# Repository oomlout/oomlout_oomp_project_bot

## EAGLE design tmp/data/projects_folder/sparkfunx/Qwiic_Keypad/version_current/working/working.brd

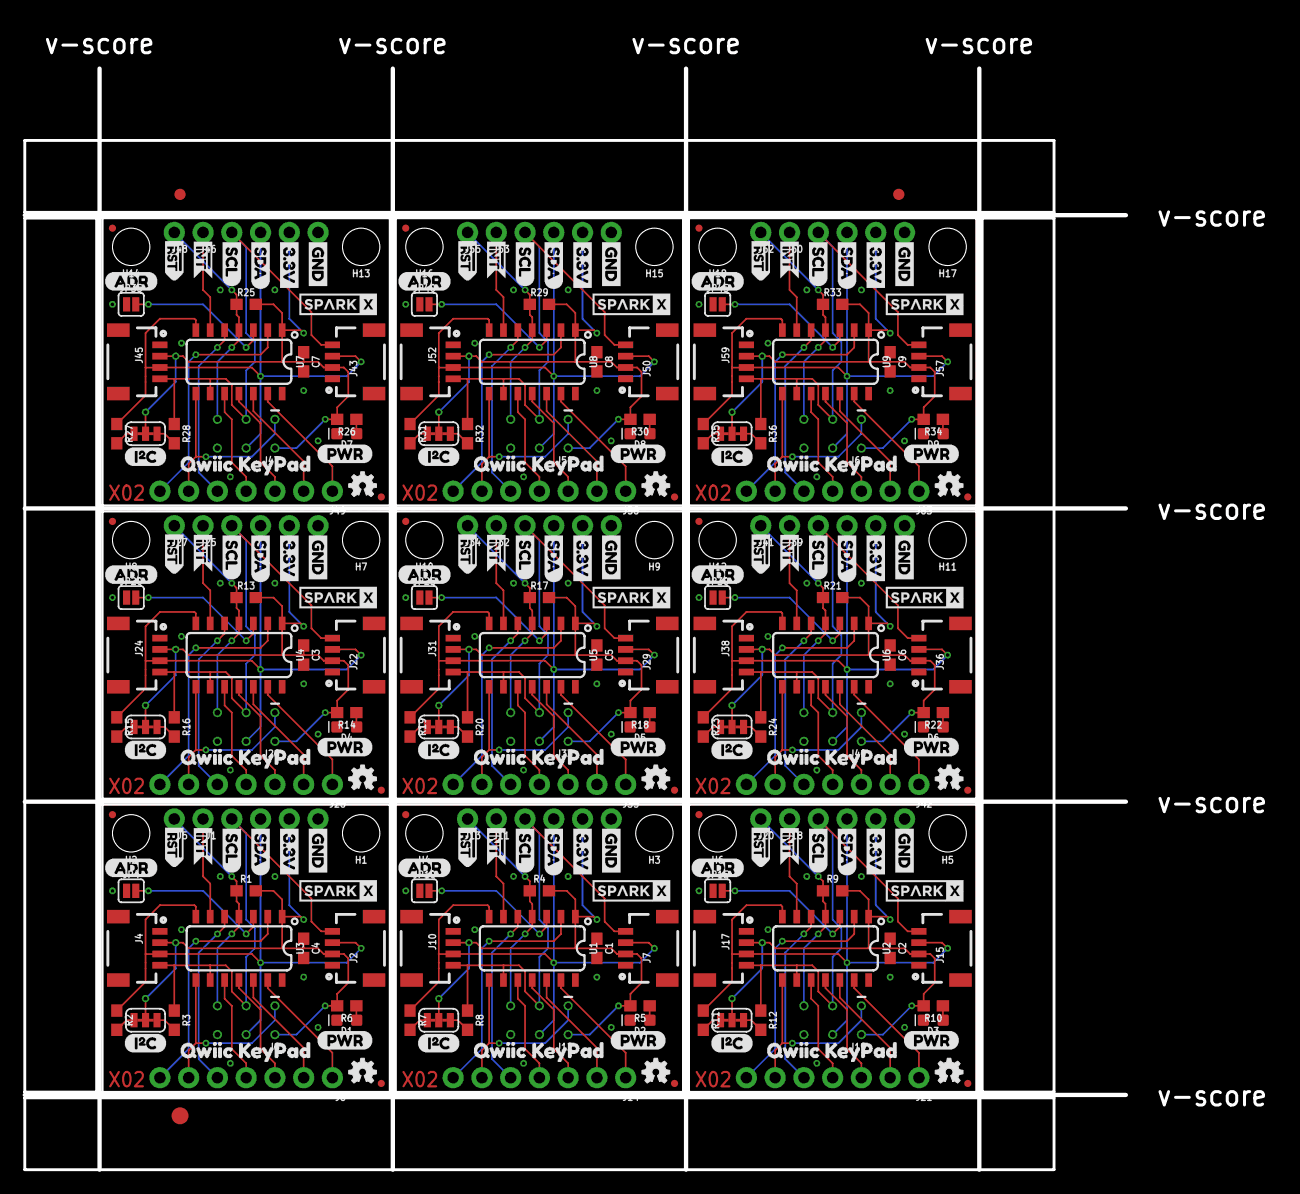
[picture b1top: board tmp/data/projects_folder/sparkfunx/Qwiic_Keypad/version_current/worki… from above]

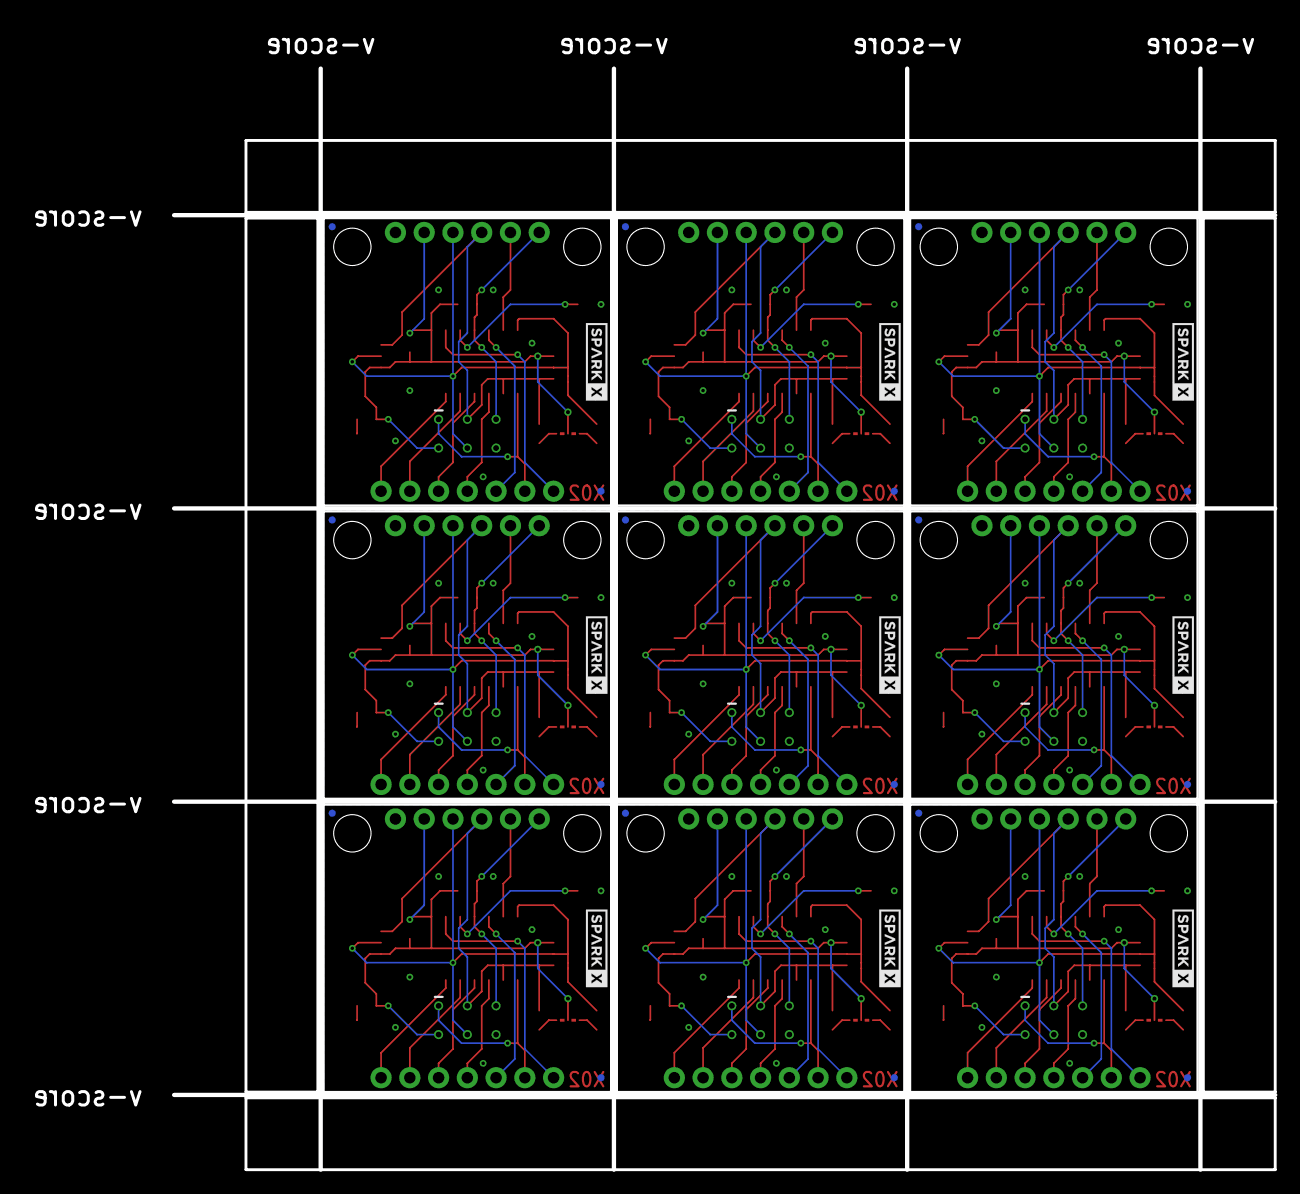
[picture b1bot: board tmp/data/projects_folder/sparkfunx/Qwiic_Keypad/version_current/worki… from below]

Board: 2 copper layers, 97.3 x 97.3 mm, 318 parts (27 on the bottom side), 153 nets.

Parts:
C1, C2, C3, C4, C5, C6, C7, C8, C9: 0.1uF; 0603
D1, D2, D3, D4, D5, D6, D7, D8, D9: RED; LED-0603
E$1, E$2: FIDUCIAL-1X2
E$3: FIDUCIAL-1.5X3
H1, H2, H3, H4, H5, H6, H7, H8, H9, H10, H11, H12, H13, H14, H15, H16, H17, H18: STAND-OFF
J1, J5, J11, J13, J18, J20, J25, J27, J32, J34, J39, J41, J46, J48, J53, J55, J60, J62: 1X01_NO_SILK
J2, J4, J7, J10, J15, J17, J22, J24, J29, J31, J36, J38, J43, J45, J50, J52, J57, J59: 1X04_1MM_RA
J3, J9, J16, J23, J30, J37, J44, J51, J58: PTH; 1X04_NO_SILK
J6, J12, J19, J26, J33, J40, J47, J54, J61: AVR_SPI_PROG_3X2TESTPOINTS; 2X3_TEST_POINTS
J8, J14, J21, J28, J35, J42, J49, J56, J63: 1X07_NO_SILK
JP1, JP2, JP3, JP5, JP6, JP7, JP8, JP9, JP11, JP12, JP13, JP14, JP16, JP17, JP18, JP19, JP21, JP22, JP23, JP24, JP26, JP27, JP28, JP29, JP31, JP32, JP33, JP34, JP36, JP37, JP38, JP39, JP41, JP42, JP43, JP44: FIDUCIALUFIDUCIAL; MICRO-FIDUCIAL
JP4, JP10, JP15, JP20, JP25, JP30, JP35, JP40, JP45: SMT-JUMPER_2_NO_SILK
LOGO1, LOGO2, LOGO3, LOGO4, LOGO5, LOGO6, LOGO7, LOGO8, LOGO9: OSHW-LOGOMINI; OSHW-LOGO-MINI
R1, R4, R9, R13, R17, R21, R25, R29, R33: 4.7k; 0603
R2, R3, R7, R8, R11, R12, R15, R16, R19, R20, R23, R24, R27, R28, R31, R32, R35, R36: 2.2k; 0603
R5, R6, R10, R14, R18, R22, R26, R30, R34: 1k; 0603
SJ1, SJ2, SJ3, SJ4, SJ5, SJ6, SJ7, SJ8, SJ9: SMT-JUMPER_3_2-NC_TRACE_SILK
U1, U2, U3, U4, U5, U6, U7, U8, U9: ATTINY84; SO14
U$1, U$2, U$7, U$13, U$25, U$26, U$37, U$38, U$49, U$50, U$61, U$62, U$73, U$74, U$85, U$86, U$97, U$98: SPARKX-LOGO3; SPARKX-SMALL
U$3, U$14, U$27, U$39, U$51, U$63, U$75, U$87, U$99: 3.3V
U$4, U$16, U$28, U$40, U$52, U$64, U$76, U$88, U$100: GND
U$5, U$17, U$29, U$41, U$53, U$65, U$77, U$89, U$101: SDA
U$6, U$18, U$30, U$42, U$54, U$66, U$78, U$90, U$102: SCL
U$8, U$19, U$31, U$43, U$55, U$67, U$79, U$91, U$103: (PWR)
U$9, U$20, U$32, U$44, U$56, U$68, U$80, U$92, U$104: (I_SUPER2_C)
U$10, U$21, U$33, U$45, U$57, U$69, U$81, U$93, U$105: (ADR)
U$11, U$22, U$34, U$46, U$58, U$70, U$82, U$94, U$106: #RST>
U$12, U$24, U$36, U$48, U$60, U$72, U$84, U$96, U$108: #INT1
U$15, U$23, U$35, U$47, U$59, U$71, U$83, U$95, U$107: QWIIC_KEYPAD0

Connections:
1: J8.1, U3.13
2: J8.2, U3.12
3: J8.3, U3.11
3.3V: C4.1, J2.2, J3.2, J4.2, J6.2, R1.2, R6.2, SJ5.2, U3.1
3.3V1: C1.1, J7.2, J9.2, J10.2, J12.2, R4.2, R5.2, SJ1.2, U1.1
3.3V2: C2.1, J15.2, J16.2, J17.2, J19.2, R9.2, R10.2, SJ2.2, U2.1
3.3V3: C3.1, J22.2, J23.2, J24.2, J26.2, R13.2, R14.2, SJ3.2, U4.1
3.3V4: C5.1, J29.2, J30.2, J31.2, J33.2, R17.2, R18.2, SJ4.2, U5.1
3.3V5: C6.1, J36.2, J37.2, J38.2, J40.2, R21.2, R22.2, SJ6.2, U6.1
3.3V6: C7.1, J43.2, J44.2, J45.2, J47.2, R25.2, R26.2, SJ7.2, U7.1
3.3V7: C8.1, J50.2, J51.2, J52.2, J54.2, R29.2, R30.2, SJ8.2, U8.1
3.3V8: C9.1, J57.2, J58.2, J59.2, J61.2, R33.2, R34.2, SJ9.2, U9.1
4: J8.4, U3.10
5: J8.5, U3.5
6: J14.4, U1.10
7: J8.7, U3.2
8: J14.3, U1.11
9: J14.2, U1.12
10: J14.1, U1.13
11: J14.7, U1.2
12: J14.5, U1.5
13: J21.4, U2.10
14: J21.3, U2.11
15: J21.2, U2.12
16: J21.1, U2.13
17: J21.7, U2.2
18: J21.5, U2.5
19: J28.4, U4.10
20: J28.3, U4.11
21: J28.2, U4.12
22: J28.1, U4.13
23: J28.7, U4.2
24: J28.5, U4.5
25: J35.4, U5.10
26: J35.3, U5.11
27: J35.2, U5.12
28: J35.1, U5.13
29: J35.7, U5.2
30: J35.5, U5.5
31: J42.4, U6.10
32: J42.3, U6.11
33: J42.2, U6.12
34: J42.1, U6.13
35: J42.7, U6.2
36: J42.5, U6.5
37: J49.4, U7.10
38: J49.3, U7.11
39: J49.2, U7.12
40: J49.1, U7.13
41: J49.7, U7.2
42: J49.5, U7.5
43: J56.4, U8.10
44: J56.3, U8.11
45: J56.2, U8.12
46: J56.1, U8.13
47: J56.7, U8.2
48: J56.5, U8.5
49: J63.4, U9.10
50: J63.3, U9.11
51: J63.2, U9.12
52: J63.1, U9.13
53: J63.7, U9.2
54: J63.5, U9.5
!INT: J1.1, U3.6
!INT1: J11.1, U1.6
!INT2: J18.1, U2.6
!INT3: J25.1, U4.6
!INT4: J32.1, U5.6
!INT5: J39.1, U6.6
!INT6: J46.1, U7.6
!INT7: J53.1, U8.6
!INT8: J60.1, U9.6
!RST: J5.1, J6.5, R1.1, U3.4
!RST1: J12.5, J13.1, R4.1, U1.4
!RST2: J19.5, J20.1, R9.1, U2.4
!RST3: J26.5, J27.1, R13.1, U4.4
!RST4: J33.5, J34.1, R17.1, U5.4
!RST5: J40.5, J41.1, R21.1, U6.4
!RST6: J47.5, J48.1, R25.1, U7.4
!RST7: J54.5, J55.1, R29.1, U8.4
!RST8: J61.5, J62.1, R33.1, U9.4
ADD1: JP4.2, U3.3
ADD2: JP10.2, U1.3
ADD3: JP15.2, U2.3
ADD4: JP20.2, U4.3
ADD5: JP25.2, U5.3
ADD6: JP30.2, U6.3
ADD7: JP35.2, U7.3
ADD8: JP40.2, U8.3
ADD9: JP45.2, U9.3
GND: C4.2, D1.C, J2.1, J3.1, J4.1, J6.6, JP4.1, U3.14
GND1: C1.2, D2.C, J7.1, J9.1, J10.1, J12.6, JP10.1, U1.14
GND2: C2.2, D3.C, J15.1, J16.1, J17.1, J19.6, JP15.1, U2.14
GND3: C3.2, D4.C, J22.1, J23.1, J24.1, J26.6, JP20.1, U4.14
GND4: C5.2, D5.C, J29.1, J30.1, J31.1, J33.6, JP25.1, U5.14
GND5: C6.2, D6.C, J36.1, J37.1, J38.1, J40.6, JP30.1, U6.14
GND6: C7.2, D7.C, J43.1, J44.1, J45.1, J47.6, JP35.1, U7.14
GND7: C8.2, D8.C, J50.1, J51.1, J52.1, J54.6, JP40.1, U8.14
GND8: C9.2, D9.C, J57.1, J58.1, J59.1, J61.6, JP45.1, U9.14
MISO/1: J12.1, J14.6, U1.8
MISO/2: J19.1, J21.6, U2.8
MISO/3: J26.1, J28.6, U4.8
MISO/4: J33.1, J35.6, U5.8
MISO/5: J40.1, J42.6, U6.8
MISO/6: J6.1, J8.6, U3.8
MISO/7: J47.1, J49.6, U7.8
MISO/8: J54.1, J56.6, U8.8
MISO/9: J61.1, J63.6, U9.8
unnamed: D1.A, R6.1
unnamed: R2.2, SJ5.3
unnamed: R3.2, SJ5.1
unnamed: D2.A, R5.1
unnamed: R7.2, SJ1.3
unnamed: R8.2, SJ1.1
unnamed: D3.A, R10.1
unnamed: R11.2, SJ2.3
unnamed: R12.2, SJ2.1
unnamed: D4.A, R14.1
unnamed: R15.2, SJ3.3
unnamed: R16.2, SJ3.1
unnamed: D5.A, R18.1
unnamed: R19.2, SJ4.3
unnamed: R20.2, SJ4.1
unnamed: D6.A, R22.1
unnamed: R23.2, SJ6.3
unnamed: R24.2, SJ6.1
unnamed: D7.A, R26.1
unnamed: R27.2, SJ7.3
unnamed: R28.2, SJ7.1
unnamed: D8.A, R30.1
unnamed: R31.2, SJ8.3
unnamed: R32.2, SJ8.1
unnamed: D9.A, R34.1
unnamed: R35.2, SJ9.3
unnamed: R36.2, SJ9.1
SCL: J2.4, J3.4, J4.4, J6.3, R3.1, U3.9
SCL1: J7.4, J9.4, J10.4, J12.3, R8.1, U1.9
SCL2: J15.4, J16.4, J17.4, J19.3, R12.1, U2.9
SCL3: J22.4, J23.4, J24.4, J26.3, R16.1, U4.9
SCL4: J29.4, J30.4, J31.4, J33.3, R20.1, U5.9
SCL5: J36.4, J37.4, J38.4, J40.3, R24.1, U6.9
SCL6: J43.4, J44.4, J45.4, J47.3, R28.1, U7.9
SCL7: J50.4, J51.4, J52.4, J54.3, R32.1, U8.9
SCL8: J57.4, J58.4, J59.4, J61.3, R36.1, U9.9
SDA: J2.3, J3.3, J4.3, J6.4, R2.1, U3.7
SDA1: J7.3, J9.3, J10.3, J12.4, R7.1, U1.7
SDA2: J15.3, J16.3, J17.3, J19.4, R11.1, U2.7
SDA3: J22.3, J23.3, J24.3, J26.4, R15.1, U4.7
SDA4: J29.3, J30.3, J31.3, J33.4, R19.1, U5.7
SDA5: J36.3, J37.3, J38.3, J40.4, R23.1, U6.7
SDA6: J43.3, J44.3, J45.3, J47.4, R27.1, U7.7
SDA7: J50.3, J51.3, J52.3, J54.4, R31.1, U8.7
SDA8: J57.3, J58.3, J59.3, J61.4, R35.1, U9.7

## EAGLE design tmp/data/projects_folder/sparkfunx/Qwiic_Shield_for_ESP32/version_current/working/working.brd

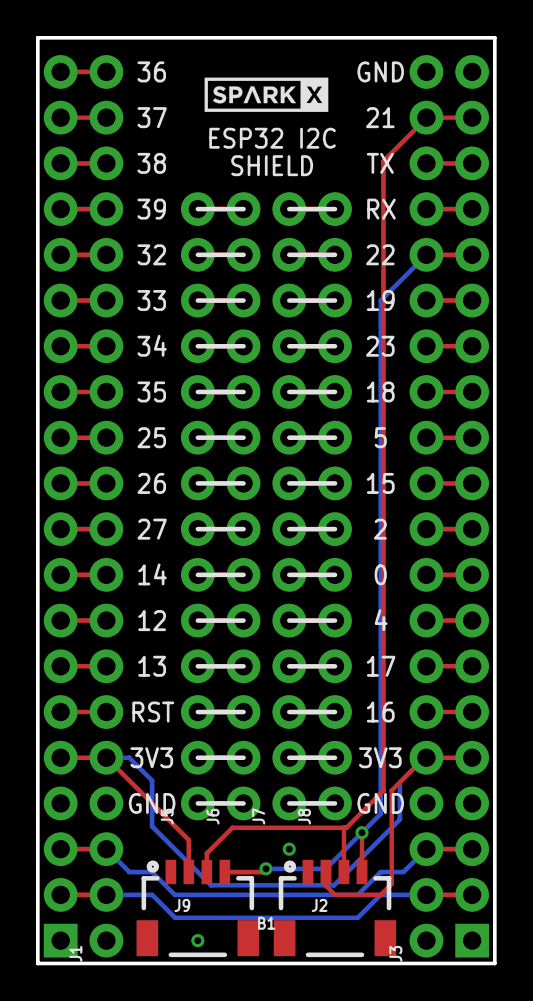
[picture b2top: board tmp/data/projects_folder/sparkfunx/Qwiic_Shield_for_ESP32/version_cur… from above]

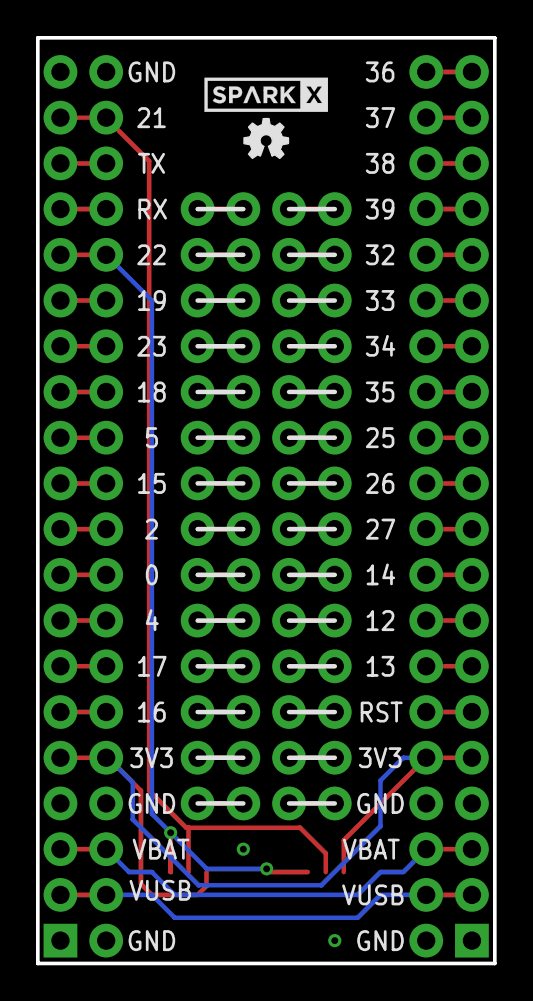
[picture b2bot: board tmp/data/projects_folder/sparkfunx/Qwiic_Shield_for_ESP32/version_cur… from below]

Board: 2 copper layers, 25.4 x 51.4 mm, 13 parts (2 on the bottom side), 61 nets.

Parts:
B1: ESP32_THING
FRAME1: FRAME-LETTERNO_PACKAGE; DUMMY
J1, J3: 1X20_NOSILK
J2, J9: 1X04_1MM_RA
J5, J6, J7, J8: 1X14_NO_SILK
LOGO1: OSHW-LOGOMINI; OSHW-LOGO-MINI
U$1, U$2: SPARKX-LOGO3; SPARKX-SMALL

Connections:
0: B1.32, J3.9
2: B1.31, J3.10
3.3V: B1.5, B1.36, J1.5, J2.2, J3.5, J9.2
4: B1.33, J3.8
5: B1.29, J3.12
12: B1.8, J1.8
13: B1.7, J1.7
14: B1.9, J1.9
15: B1.30, J3.11
16: B1.35, J3.6
17: B1.34, J3.7
25: B1.12, J1.12
26: B1.11, J1.11
27: B1.10, J1.10
32: B1.16, J1.16
33: B1.15, J1.15
34: B1.14, J1.14
35: B1.13, J1.13
36: B1.20, J1.20
37: B1.19, J1.19
38: B1.18, J1.18
39: B1.17, J1.17
GND: B1.1, B1.4, B1.21, B1.37, B1.40, J1.1, J1.4, J2.1, J3.1, J3.4, J3.20, J9.1
MISO: B1.26, J3.15
MOSI: B1.27, J3.14
unnamed: J7.1, J8.1
unnamed: J7.2, J8.2
unnamed: J7.3, J8.3
unnamed: J7.4, J8.4
unnamed: J7.5, J8.5
unnamed: J7.6, J8.6
unnamed: J7.7, J8.7
unnamed: J7.8, J8.8
unnamed: J7.9, J8.9
unnamed: J7.10, J8.10
unnamed: J7.11, J8.11
unnamed: J7.12, J8.12
unnamed: J7.13, J8.13
unnamed: J7.14, J8.14
unnamed: J5.1, J6.1
unnamed: J5.2, J6.2
unnamed: J5.3, J6.3
unnamed: J5.4, J6.4
unnamed: J5.5, J6.5
unnamed: J5.6, J6.6
unnamed: J5.7, J6.7
unnamed: J5.8, J6.8
unnamed: J5.9, J6.9
unnamed: J5.10, J6.10
unnamed: J5.11, J6.11
unnamed: J5.12, J6.12
unnamed: J5.13, J6.13
unnamed: J5.14, J6.14
RST: B1.6, J1.6
RX: B1.24, J3.17
SCK: B1.28, J3.13
SCL: B1.25, J2.4, J3.16, J9.4
SDA: B1.22, J2.3, J3.19, J9.3
TX: B1.23, J3.18
VBAT: B1.3, B1.38, J1.3, J3.3
VUSB: B1.2, B1.39, J1.2, J3.2

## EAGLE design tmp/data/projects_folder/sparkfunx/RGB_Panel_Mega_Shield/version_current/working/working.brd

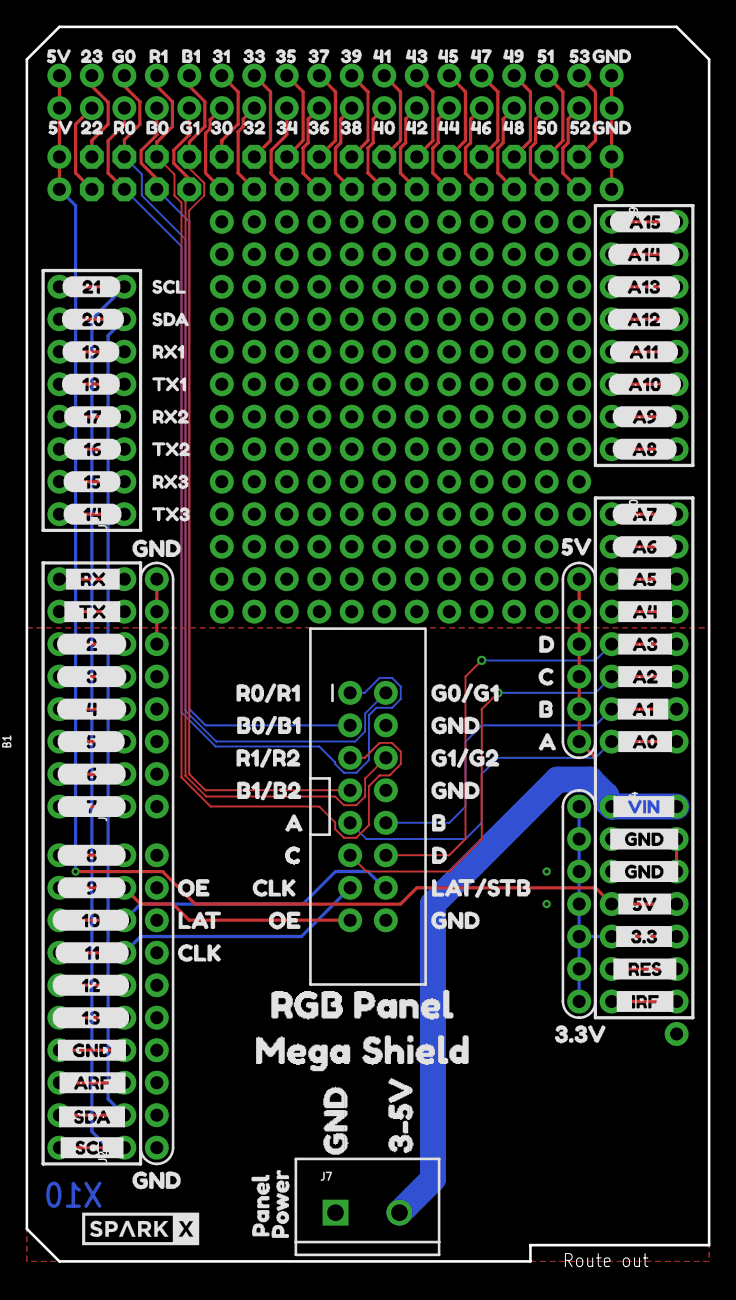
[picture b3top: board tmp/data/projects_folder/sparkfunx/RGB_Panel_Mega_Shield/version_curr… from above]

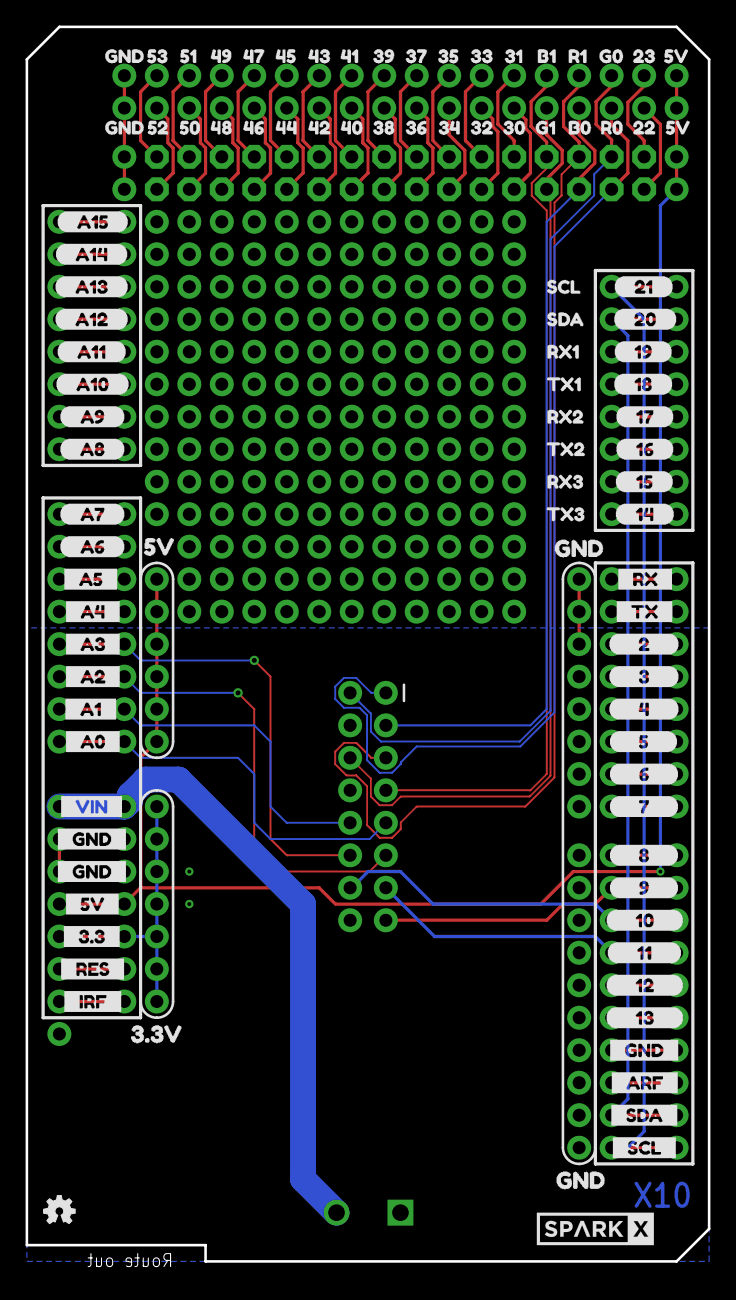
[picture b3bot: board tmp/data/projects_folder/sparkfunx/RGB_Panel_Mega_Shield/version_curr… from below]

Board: 2 copper layers, 53.3 x 96.5 mm, 240 parts (99 on the bottom side), 77 nets.

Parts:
B1: ARDUINO_MEGA_R3; ARDUINO_MEGA_NO_SILK
FRAME1: FRAME-LETTER; CREATIVE_COMMONS
J1, J5, J9, J10: 1X08_NO_SILK
J2: 1X10_NO_SILK
J4: 1X07_NO_SILK
J7: Screw Terminal; SCREWTERMINAL-5MM-2
J8: SparkFun Panel; 2X8-SHROUDED_LOCK
J11, J12: 1X18_NO_SILK
LOGO1: OSHW-LOGOMINI; OSHW-LOGO-MINI
U$1, U$34: D42
U$2, U$183: __A6__0
U$3, U$32, U$113: C37
U$4, U$38: GND48
U$5: 3#5V3
U$6, U$79: ____2____1
U$7, U$80: ____3____3
U$8, U$81: ____4____4
U$9, U$82: ____5____5
U$10, U$83: ____6____6
U$11: GND2
U$12, U$84: ____7____7
U$13, U$85: ____8____8
U$14, U$86: ____9____9
U$15, U$87: ____10____10
U$16: PANEL0
U$17, U$88: ____11____11
U$18, U$89: ____12____12
U$19: POWER1
U$20, U$90: ____13____13
U$21, U$22, U$37, U$108, U$109: GND40
U$23: RGB_PANEL2
U$24, U$73: __RX__0
U$25, U$110: 3#3V46
U$26, U$107: 5V47
U$27, U$45: __3#3__27
U$28, U$115: A36
U$29: B0#B132
U$30: B1#B235
U$31, U$114: B43
U$33, U$121: CLK38
U$35: G0#G145
U$36: G1#G244
U$39: LAT#STB41
U$40, U$122: OE39
U$41: R0#R131
U$42: R1#R234
U$43, U$48: __5V__26
U$44, U$62: __A0__23
U$46, U$63: __A1__22
U$47, U$64: __A2__21
U$49, U$65: __A3__20
U$50, U$66: __A4__19
U$51, U$72: __A5__18
U$52, U$74: __ARF__15
U$53, U$75: __GND__14
U$54, U$55, U$67, U$68: __GND__25
U$56, U$71: __IRF__29
U$57, U$69: __RES__28
U$58, U$76: __SCL__17
U$59, U$77: __SDA__16
U$60, U$78: __TX__0
U$61, U$70: __VIN__24
U$91: SPARKX-LOGO4; SPARKX-MEDIUM
U$92, U$182: __A7__0
U$93, U$191: __A8__1
U$94, U$190: __A9__2
U$95, U$184: __A10__3
U$96, U$185: __A11__4
U$97, U$186: __A12__5
U$98, U$187: __A13__6
U$99, U$188: __A14__7
U$100, U$189: __A15__8
U$101, U$112: __14__0
U$102, U$116: __15__1
U$103, U$117: __16__2
U$104, U$118: __17__3
U$105, U$119: __18__4
U$106, U$120: __19__5
U$111, U$132: __20__6
U$123: LAT0
U$124: SHIELD0
U$125, U$134: __21__7
U$126, U$136: TX30
U$127, U$175: SDA2
U$128: SPARKX-MEDIUM
U$129, U$176: SCL3
U$130, U$177: RX31
U$131: MEGA4
U$133, U$223: 2232
U$135, U$137, U$205, U$224: GND0
U$138, U$178: RX14
U$139, U$179: RX22
U$140, U$180: TX13
U$141, U$181: TX21
U$142, U$143, U$192, U$210: 5V1
U$144, U$211: 469
U$145, U$193: 478
U$146, U$212: 487
U$147, U$194: 496
U$148, U$213: 505
U$149, U$195: 514
U$150, U$214: 523
U$151, U$196: 532
U$152, U$215: 3025
U$153, U$197: 3124
U$154, U$216: 3223
U$155, U$198: 3322
U$156, U$217: 3421
U$157, U$199: 3520
U$158, U$218: 3619
U$159, U$200: 3718
U$160, U$219: 3817
U$161, U$201: 3916
U$162, U$220: 4015
U$163, U$202: 4114
U$164, U$221: 4213
U$165, U$203: 4312
U$166, U$222: 4411
U$167, U$204: 4510
U$168, U$206: 230
U$169, U$225: B02
U$170, U$207: B14
U$171, U$208: G05
U$172, U$226: G16
U$173, U$227: R01
U$174, U$209: R13

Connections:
0(RX0): B1.0, J1.8
1(TX0): B1.1, J1.7
2: B1.2, J1.6
3: B1.3, J1.5
3.3V: B1.3.3V, J4.5
4: B1.4, J1.4
5: B1.5, J1.3
5V: B1.5V, B1.5V@1, B1.5V@2, J4.4, J11.18, J12.1
6: B1.6, J1.2
7: B1.7, J1.1
8: B1.8, J2.10
12: B1.12, J2.6
13: B1.13, J2.5
14: B1.14, J5.1
15: B1.15, J5.2
16: B1.16, J5.3
17: B1.17, J5.4
18: B1.18, J5.5
19: B1.19, J5.6
22: B1.22, J12.2
23: B1.23, J11.17
30: B1.30, J12.6
31: B1.31, J11.13
32: B1.32, J12.7
33: B1.33, J11.12
34: B1.34, J12.8
35: B1.35, J11.11
36: B1.36, J12.9
37: B1.37, J11.10
38: B1.38, J12.10
39: B1.39, J11.9
40: B1.40, J12.11
41: B1.41, J11.8
42: B1.42, J12.12
43: B1.43, J11.7
44: B1.44, J12.13
45: B1.45, J11.6
46: B1.46, J12.14
47: B1.47, J11.5
48: B1.48, J12.15
49: B1.49, J11.4
50/MISO: B1.50, J12.16
51/MOSI: B1.51, J11.3
52/SCK: B1.52, J12.17
53/!CS: B1.53, J11.2
!RESET: B1.RESET, J4.6
A: B1.A0, J8.9, J10.8
A4: B1.A4, J10.4
A5: B1.A5, J10.3
A6: B1.A6, J10.2
A7: B1.A7, J10.1
A8: B1.A8, J9.8
A9: B1.A9, J9.7
A10: B1.A10, J9.6
A11: B1.A11, J9.5
A12: B1.A12, J9.4
A13: B1.A13, J9.3
A14: B1.A14, J9.2
A15: B1.A15, J9.1
AREF: B1.AREF, J2.3
B: B1.A1, J8.10, J10.7
B0: B1.26, J8.3, J12.4
B1: B1.29, J8.7, J11.14
C: B1.A2, J8.11, J10.6
CLK: B1.11, J2.7, J8.13
D: B1.A3, J8.12, J10.5
G0: B1.25, J8.2, J11.16
G1: B1.28, J8.6, J12.5
GND: B1.GND, B1.GND@1, B1.GND@2, B1.GND@3, B1.GND@4, J2.4, J4.2, J4.3, J7.1, J8.4, J8.8, J8.16, J11.1, J12.18
IOREF: B1.IOREF, J4.7
LAT: B1.10, J2.8, J8.14
OE: B1.9, J2.9, J8.15
R0: B1.24, J8.1, J12.3
R1: B1.27, J8.5, J11.15
SCL: B1.21, B1.SCL, J2.1, J5.8
SDA: B1.20, B1.SDA, J2.2, J5.7
VIN: B1.VIN, J4.1, J7.2

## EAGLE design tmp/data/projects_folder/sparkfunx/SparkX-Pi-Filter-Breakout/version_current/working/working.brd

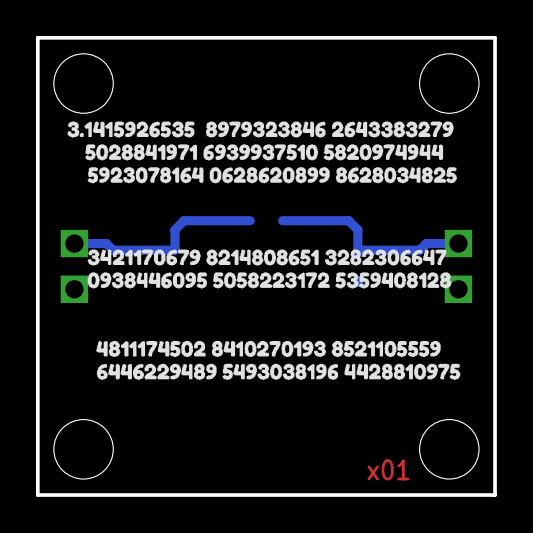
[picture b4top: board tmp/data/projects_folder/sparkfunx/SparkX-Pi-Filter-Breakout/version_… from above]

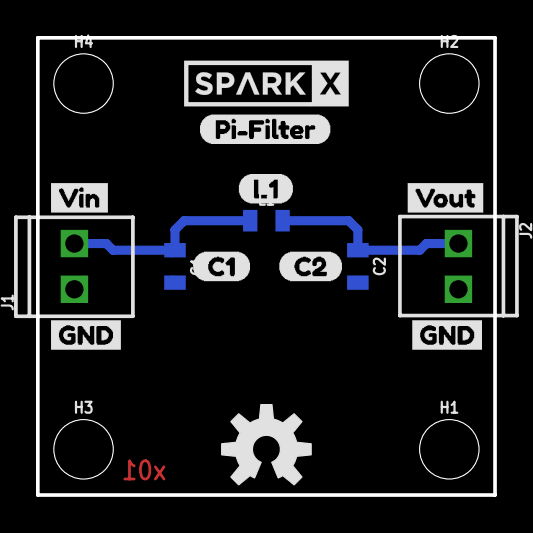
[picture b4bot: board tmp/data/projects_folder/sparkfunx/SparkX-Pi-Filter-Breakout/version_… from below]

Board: 2 copper layers, 25.4 x 25.4 mm, 27 parts (20 on the bottom side), 3 nets.

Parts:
C1, C2: DNP; 0805
FRAME1: FRAME-LETTER; CREATIVE_COMMONS
H1, H2, H3, H4: STAND-OFF
J1, J2: 1X02_2.54_SCREWTERM
L1: DNP; 0805
LOGO1: OSHW-LOGOM; OSHW-LOGO-M
U$1: SPARKX-LOGO4; SPARKX-MEDIUM
U$2, U$3: GND0
U$4: PI#FILTER3
U$5: VIN1
U$6: 3#1415926535__8979323846_26433832790
U$7: 5028841971_6939937510_58209749441
U$8: 5923078164_0628620899_86280348252
U$9: 3421170679_8214808651_32823066473
U$10: 0938446095_5058223172_53594081284
U$11: 4811174502_8410270193_85211055595
U$12: 6446229489_5493038196_44288109756
U$13: VOUT2
U$14: C10
U$15: C21
U$16: L12

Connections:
GND: C1.2, C2.2, J1.P2, J2.P1
unnamed: C1.1, J1.P1, L1.1
unnamed: C2.1, J2.P2, L1.2

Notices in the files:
parts and their libraries:
SparkFun-Resistors: Licensing: Creative Commons ShareAlike 4.0 International - https://creativecommons.org/licenses/by-sa/4.0
SparkFun-Aesthetics: Licensing: CC v3.0 Share-Alike You are welcome to use this library for commercial purposes.
